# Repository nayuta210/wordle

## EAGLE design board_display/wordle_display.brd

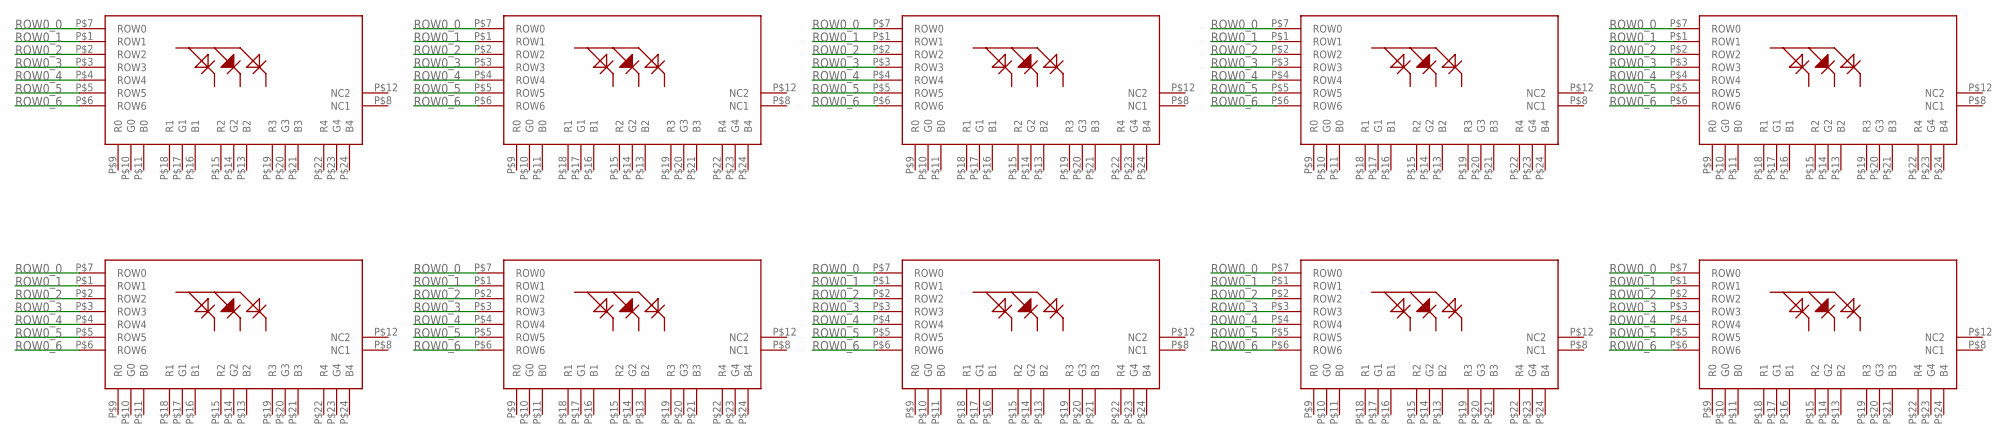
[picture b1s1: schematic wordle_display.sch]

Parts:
U$1, U$2, U$3, U$4, U$5, U$6, U$7, U$8, U$9, U$10: AE-UDOTMATRIX5X7-RGB

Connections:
ROW0_0: U$1.P$7 (ROW0), U$2.P$7 (ROW0), U$3.P$7 (ROW0), U$4.P$7 (ROW0), U$5.P$7 (ROW0), U$6.P$7 (ROW0), U$7.P$7 (ROW0), U$8.P$7 (ROW0), U$9.P$7 (ROW0), U$10.P$7 (ROW0)
ROW0_1: U$1.P$1 (ROW1), U$2.P$1 (ROW1), U$3.P$1 (ROW1), U$4.P$1 (ROW1), U$5.P$1 (ROW1), U$6.P$1 (ROW1), U$7.P$1 (ROW1), U$8.P$1 (ROW1), U$9.P$1 (ROW1), U$10.P$1 (ROW1)
ROW0_2: U$1.P$2 (ROW2), U$2.P$2 (ROW2), U$3.P$2 (ROW2), U$4.P$2 (ROW2), U$5.P$2 (ROW2), U$6.P$2 (ROW2), U$7.P$2 (ROW2), U$8.P$2 (ROW2), U$9.P$2 (ROW2), U$10.P$2 (ROW2)
ROW0_3: U$1.P$3 (ROW3), U$2.P$3 (ROW3), U$3.P$3 (ROW3), U$4.P$3 (ROW3), U$5.P$3 (ROW3), U$6.P$3 (ROW3), U$7.P$3 (ROW3), U$8.P$3 (ROW3), U$9.P$3 (ROW3), U$10.P$3 (ROW3)
ROW0_4: U$1.P$4 (ROW4), U$2.P$4 (ROW4), U$3.P$4 (ROW4), U$4.P$4 (ROW4), U$5.P$4 (ROW4), U$6.P$4 (ROW4), U$7.P$4 (ROW4), U$8.P$4 (ROW4), U$9.P$4 (ROW4), U$10.P$4 (ROW4)
ROW0_5: U$1.P$5 (ROW5), U$2.P$5 (ROW5), U$3.P$5 (ROW5), U$4.P$5 (ROW5), U$5.P$5 (ROW5), U$6.P$5 (ROW5), U$7.P$5 (ROW5), U$8.P$5 (ROW5), U$9.P$5 (ROW5), U$10.P$5 (ROW5)
ROW0_6: U$1.P$6 (ROW6), U$2.P$6 (ROW6), U$3.P$6 (ROW6), U$4.P$6 (ROW6), U$5.P$6 (ROW6), U$6.P$6 (ROW6), U$7.P$6 (ROW6), U$8.P$6 (ROW6), U$9.P$6 (ROW6), U$10.P$6 (ROW6)

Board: 2 copper layers, 10 parts (0 on the bottom side), 7 nets, no tracks yet.
